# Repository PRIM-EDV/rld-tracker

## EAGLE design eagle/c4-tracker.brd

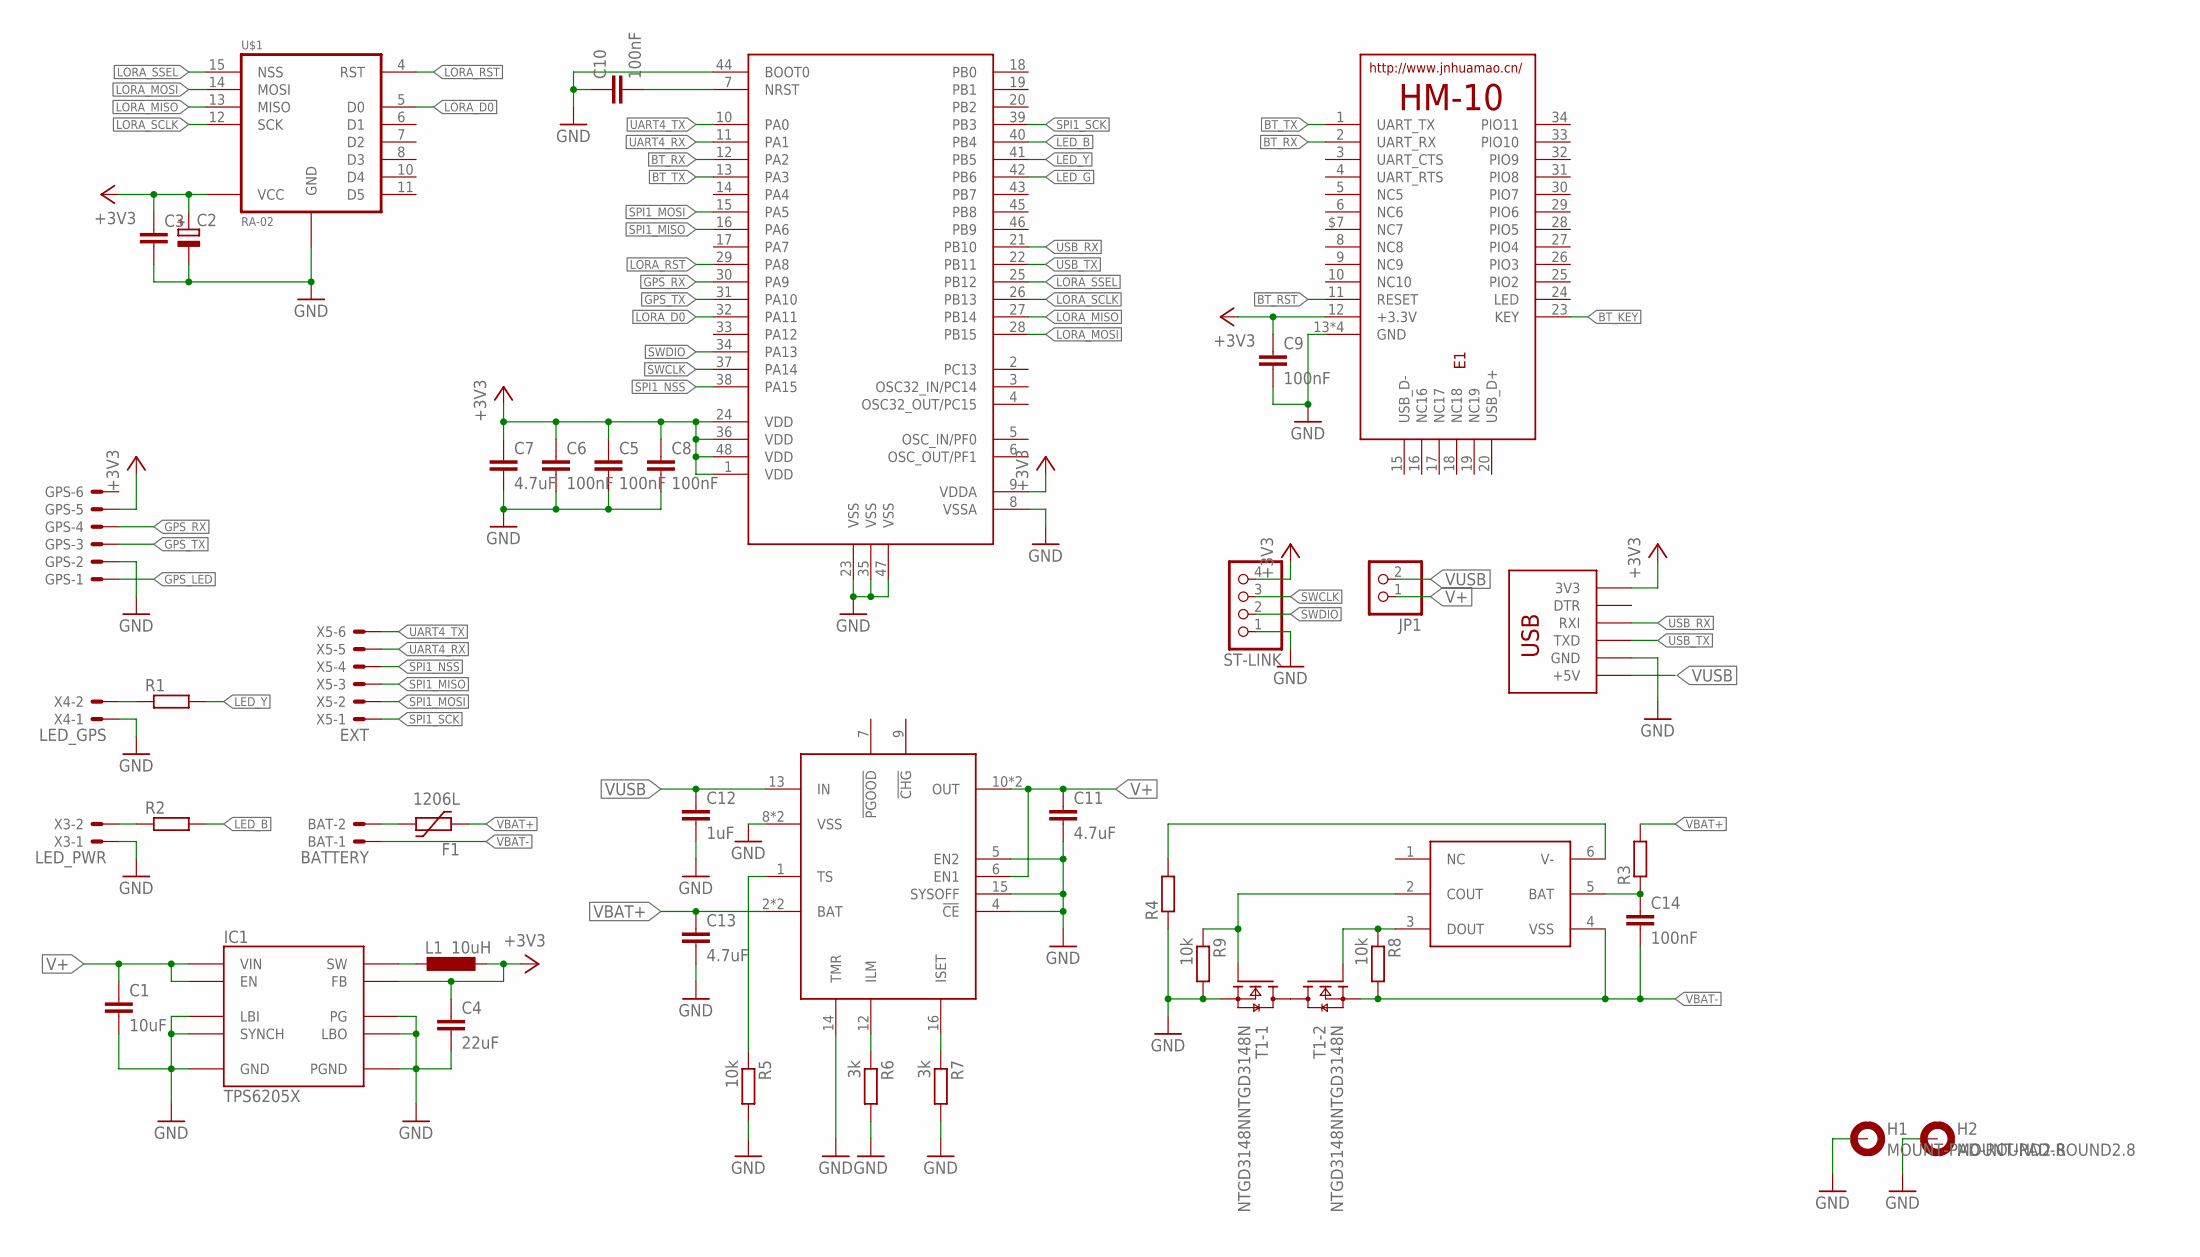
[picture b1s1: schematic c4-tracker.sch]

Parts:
BAT: BATTERY; 53261-02
C1: 10uF; C0805
C2: CPOL-EUC; PANASONIC_C
C3: C-EUC0805; C0805
C4: 22uF; C0805
C5, C6, C8, C9, C10, C14: 100nF; C0805
C7, C11, C13: 4.7uF; C0805
C12: 1uF; C0805
E1: HM-10-BOARD; 26.9X13X2.2_BOARD
F1: 1206L
GPS: 53398-06
H1, H2: MOUNT-PAD-ROUND2.8; 2,8-PAD
IC1: TPS6205X; VSSOP10
IC2: BQ24075/9T; VQFN16
JP1: PINHD-1X2; 1X02
L1: 10uH; CDRH5D28R
MC1: STM32F030CC-48; LQFP48-7X7
R1, R2, R3, R4: R-EU_R0805; R0805
R5, R8, R9: 10k; R0805
R6, R7: 3k; R0805
ST-LINK: PINHD-1X4; 1X04
T1: NTGD3148NNTGD3148N; TSOP-6
U$1: RA-02; RA-01/RA-02
U$2: RS232_USB; CP2102_MICRO_USB_BOARD
U$3: BQ2970; WSON6
X3: LED_PWR; 53261-02
X4: LED_GPS; 53261-02
X5: EXT; 53261-06

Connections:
+3V3: C2.+, C3.1, C4.1, C5.1, C6.1, C7.1, C8.1, C9.1, E1.12 (+3.3V), GPS.5, IC1.P$5 (FB), L1.1, MC1.1 (VDD), MC1.9 (VDDA), MC1.24 (VDD), MC1.36 (VDD), MC1.48 (VDD), ST-LINK.4, U$1.3 (VCC), U$2.3V3
BT_KEY: E1.23 (KEY)
BT_RST: E1.11 (RESET)
BT_RX: E1.2 (UART_RX), MC1.12 (PA2)
BT_TX: E1.1 (UART_TX), MC1.13 (PA3)
GND: C1.2, C2.-, C3.2, C4.2, C5.2, C6.2, C7.2, C8.2, C9.2, C10.1, C11.2, C12.2, C13.2, E1.13 (GND), E1.14 (GND), E1.21 (GND), E1.22 (GND), GPS.2, H1.B2,8, H2.B2,8, IC1.P$2 (LBO), IC1.P$3 (GND), IC1.P$4 (PG), IC1.P$6 (LBI), IC1.P$7 (SYNCH), IC1.P$10 (PGND), IC2.4 (!CE), IC2.5 (EN2), IC2.8 (VSS), IC2.14 (TMR), IC2.15 (SYSOFF), IC2.17 (VSS), MC1.8 (VSSA), MC1.23 (VSS), MC1.35 (VSS), MC1.44 (BOOT0), MC1.47 (VSS), R4.1, R5.2, R6.2, R7.2, R9.2, ST-LINK.1, T1.5 (S), U$1.1 (GND), U$1.2 (GND), U$1.9 (GND), U$1.16 (GND), U$2.GND, X3.1, X4.1
GPS_LED: GPS.1
GPS_RX: GPS.4, MC1.30 (PA9)
GPS_TX: GPS.3, MC1.31 (PA10)
LED_B: MC1.40 (PB4), R2.2
LED_G: MC1.42 (PB6)
LED_Y: MC1.41 (PB5), R1.2
LORA_D0: MC1.32 (PA11), U$1.5 (D0)
LORA_MISO: MC1.27 (PB14), U$1.13 (MISO)
LORA_MOSI: MC1.28 (PB15), U$1.14 (MOSI)
LORA_RST: MC1.29 (PA8), U$1.4 (RST)
LORA_SCLK: MC1.26 (PB13), U$1.12 (SCK)
LORA_SSEL: MC1.25 (PB12), U$1.15 (NSS)
unnamed: C14.1, R3.1, U$3.5 (BAT)
unnamed: IC1.P$9 (SW), L1.2
unnamed: IC2.12 (ILM), R6.1
unnamed: R1.1, X4.2
unnamed: BAT.2, F1.P$2 (2)
unnamed: R2.1, X3.2
unnamed: R4.2, U$3.6 (V-)
unnamed: R9.1, T1.1 (G), U$3.2 (COUT)
unnamed: T1.4 (D), T1.6 (D)
unnamed: R8.1, T1.3 (G), U$3.3 (DOUT)
unnamed: C10.2, MC1.7 (NRST)
unnamed: IC2.1 (TS), R5.1
unnamed: IC2.16 (ISET), R7.1
SPI1_MISO: MC1.16 (PA6), X5.3
SPI1_MOSI: MC1.15 (PA5), X5.2
SPI1_NSS: MC1.38 (PA15), X5.4
SPI1_SCK: MC1.39 (PB3), X5.1
SWCLK: MC1.37 (PA14), ST-LINK.3
SWDIO: MC1.34 (PA13), ST-LINK.2
UART4_RX: MC1.11 (PA1), X5.5
UART4_TX: MC1.10 (PA0), X5.6
USB_RX: MC1.21 (PB10), U$2.RXI
USB_TX: MC1.22 (PB11), U$2.TXD
V+: C1.1, C11.1, IC1.P$1 (VIN), IC1.P$8 (EN), IC2.6 (EN1), IC2.10 (OUT), IC2.11 (OUT), JP1.1
VBAT+: C13.1, F1.P$1 (1), IC2.2 (BAT), IC2.3 (BAT), R3.2
VBAT-: BAT.1, C14.2, R8.2, T1.2 (S), U$3.4 (VSS)
VUSB: C12.1, IC2.13 (IN), JP1.2, U$2.+5V

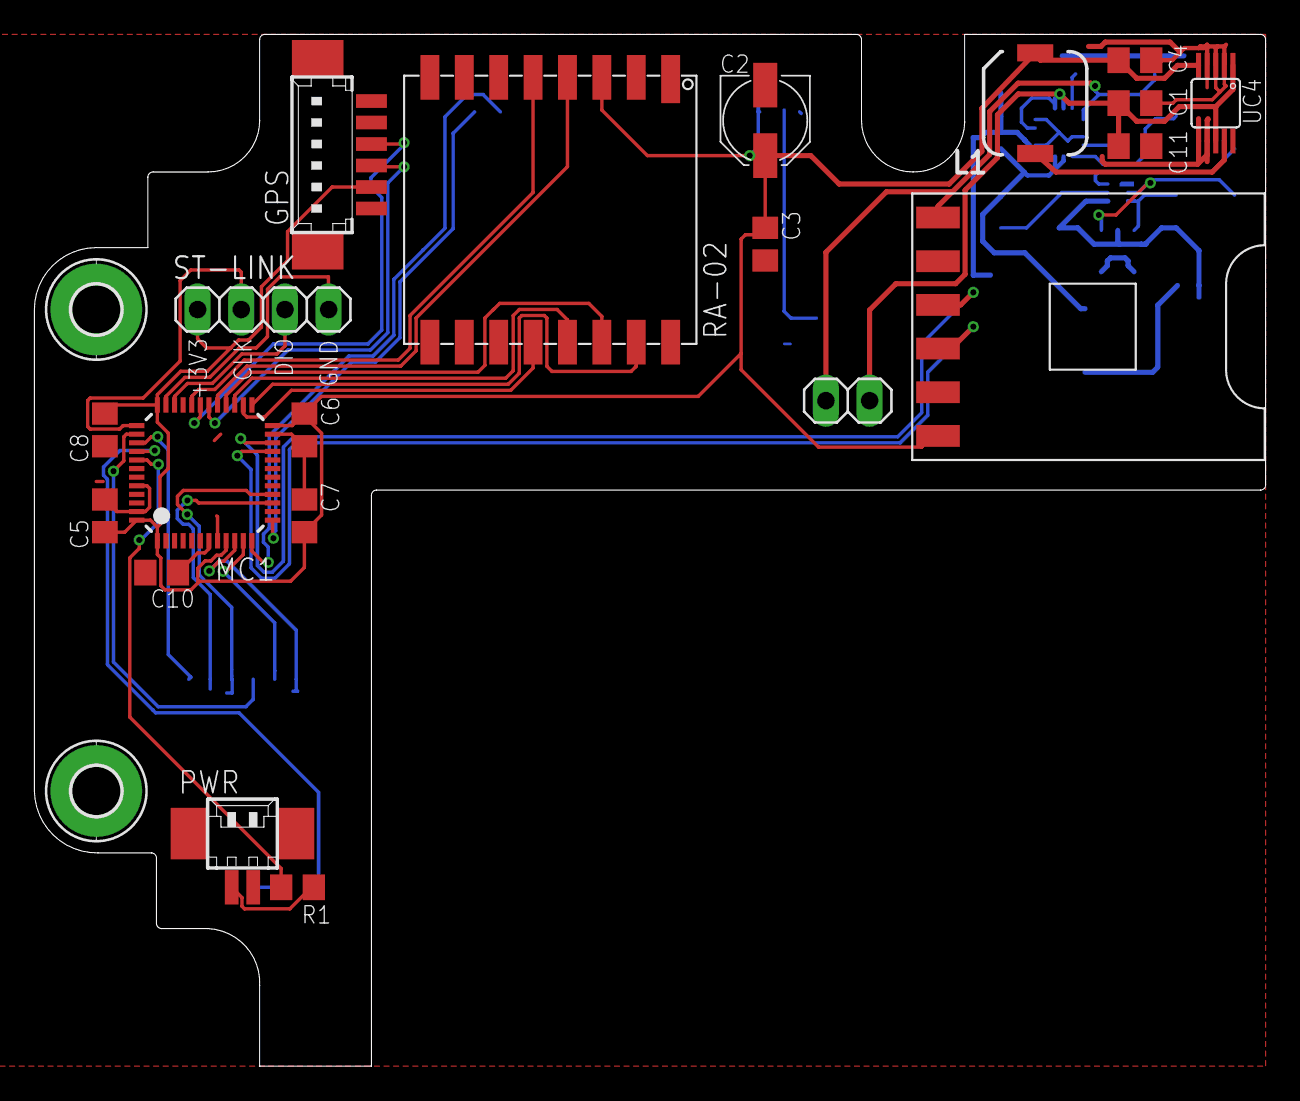
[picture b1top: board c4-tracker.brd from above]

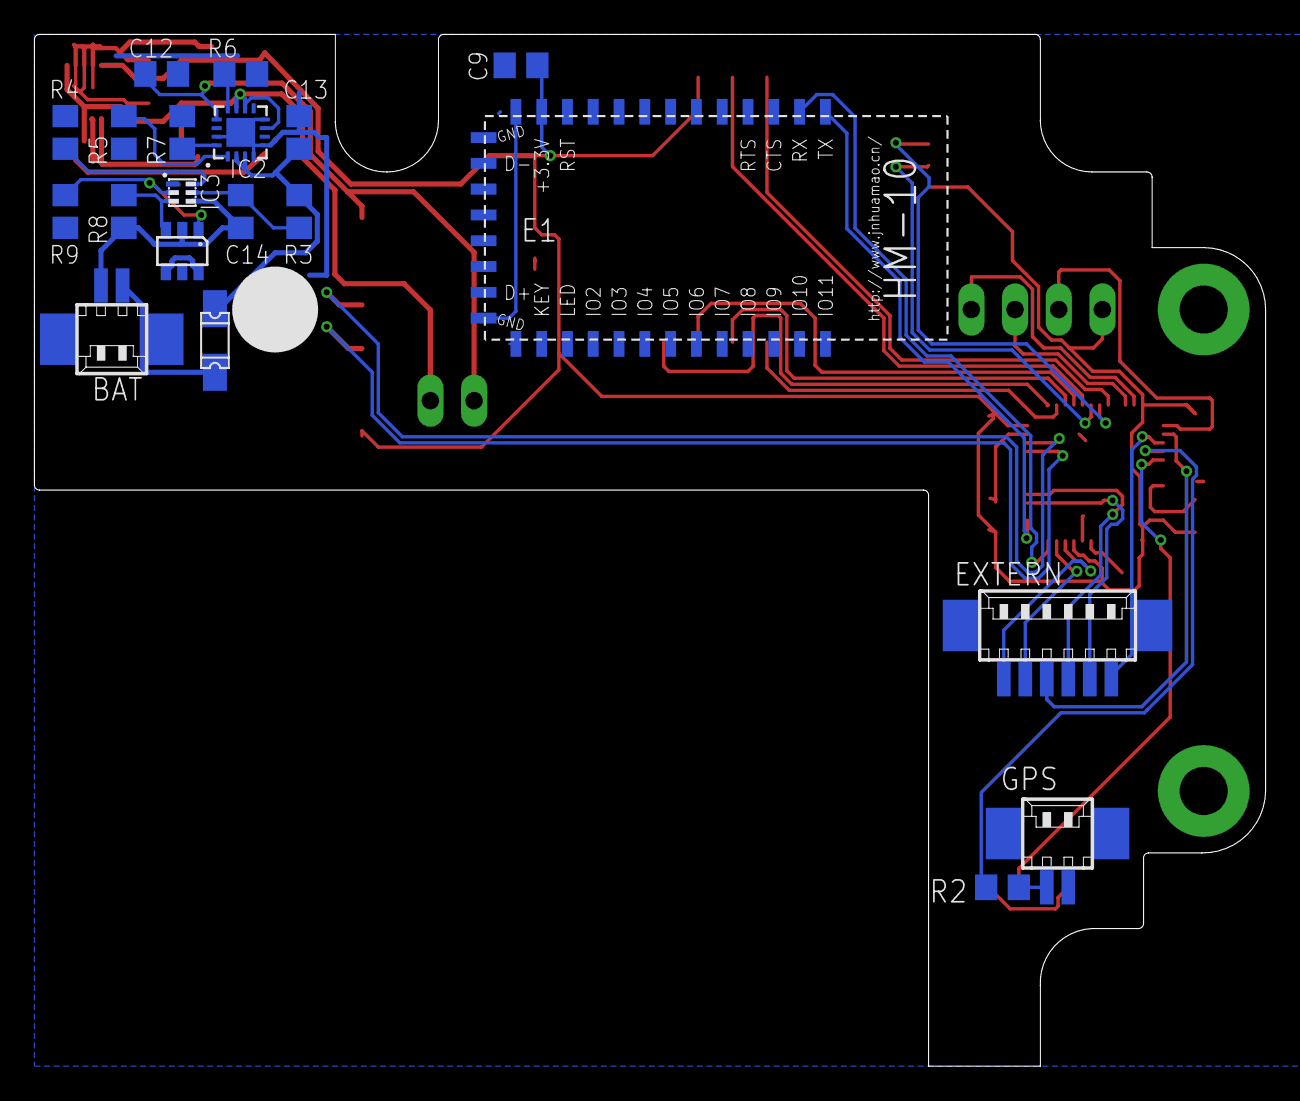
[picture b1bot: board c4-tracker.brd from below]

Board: 2 copper layers, 71.6 x 60.0 mm, 42 parts (20 on the bottom side), 41 nets.

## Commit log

2022-08-27 Create LICENSE.md
    Added LICENSE
2022-08-27 Added tracker sources
2022-08-27 Fixed old xpcc licensing in libraries
2023-05-10 Added modm and started restructuring
2023-05-10 Added ai-thinker interface and boardfile
2023-05-10 removed lora submodule
2023-05-10 re-added lora submodule
2023-05-10 Fixed submodule pathing
2023-05-10 Added lora thread
2023-05-19 Updated GPS module
2023-05-21 Added c_cpp properties and basic GPS NMEA implementation
2023-05-21 Added gps thread
2023-05-22 Fixed issues with gps thread
2023-05-23 Updated gps submodule
2023-05-23 Added shared members and updated threads
2023-05-24 Finalized basic implementation
2023-05-24 Removed old source files and alled LED support
2023-05-24 removed old source files (now for real)
2023-05-25 Added BT device name setting
